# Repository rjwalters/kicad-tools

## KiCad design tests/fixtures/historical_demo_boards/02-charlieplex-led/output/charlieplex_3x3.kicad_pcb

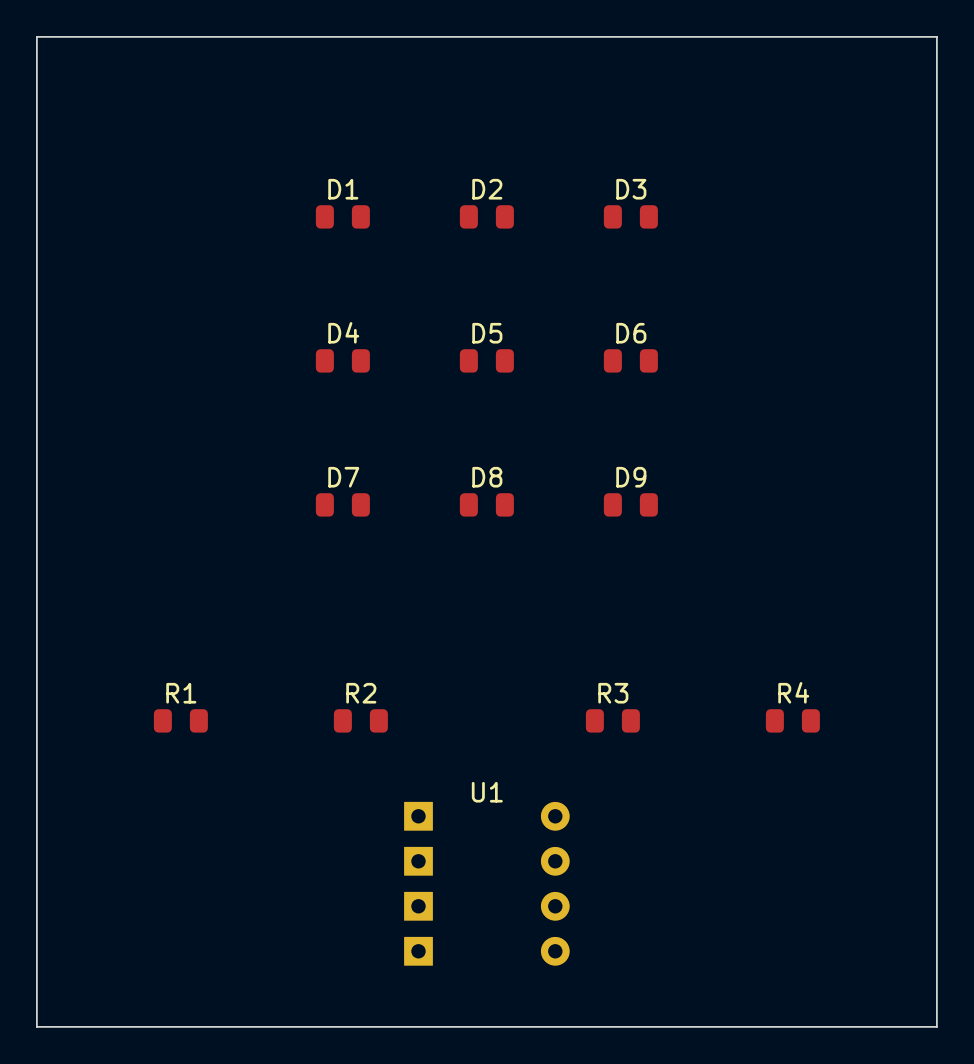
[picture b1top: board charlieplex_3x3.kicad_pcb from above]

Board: 2 copper layers, 50.0 x 55.0 mm, 14 parts (0 on the bottom side), 9 nets, no tracks yet.

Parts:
D1, D2, D3, D4, D5, D6, D7, D8, D9: LED; LED_0805_2012Metric
R1, R2, R3, R4: 330R; R_0805_2012Metric
U1: MCU; DIP-8_W7.62mm

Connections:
GND: U1.5, U1.6, U1.8
LINE_A: R1.1, U1.1
LINE_B: R2.1, U1.2
LINE_C: R3.1, U1.3
LINE_D: R4.1, U1.4
NODE_A: D1.2, D2.1, D3.2, D4.1, D5.2, D6.1, R1.2
NODE_B: D1.1, D2.2, D7.2, D8.1, D9.2, R2.2
NODE_C: D3.1, D4.2, D7.1, D8.2, R3.2
NODE_D: D5.1, D6.2, D9.1, R4.2

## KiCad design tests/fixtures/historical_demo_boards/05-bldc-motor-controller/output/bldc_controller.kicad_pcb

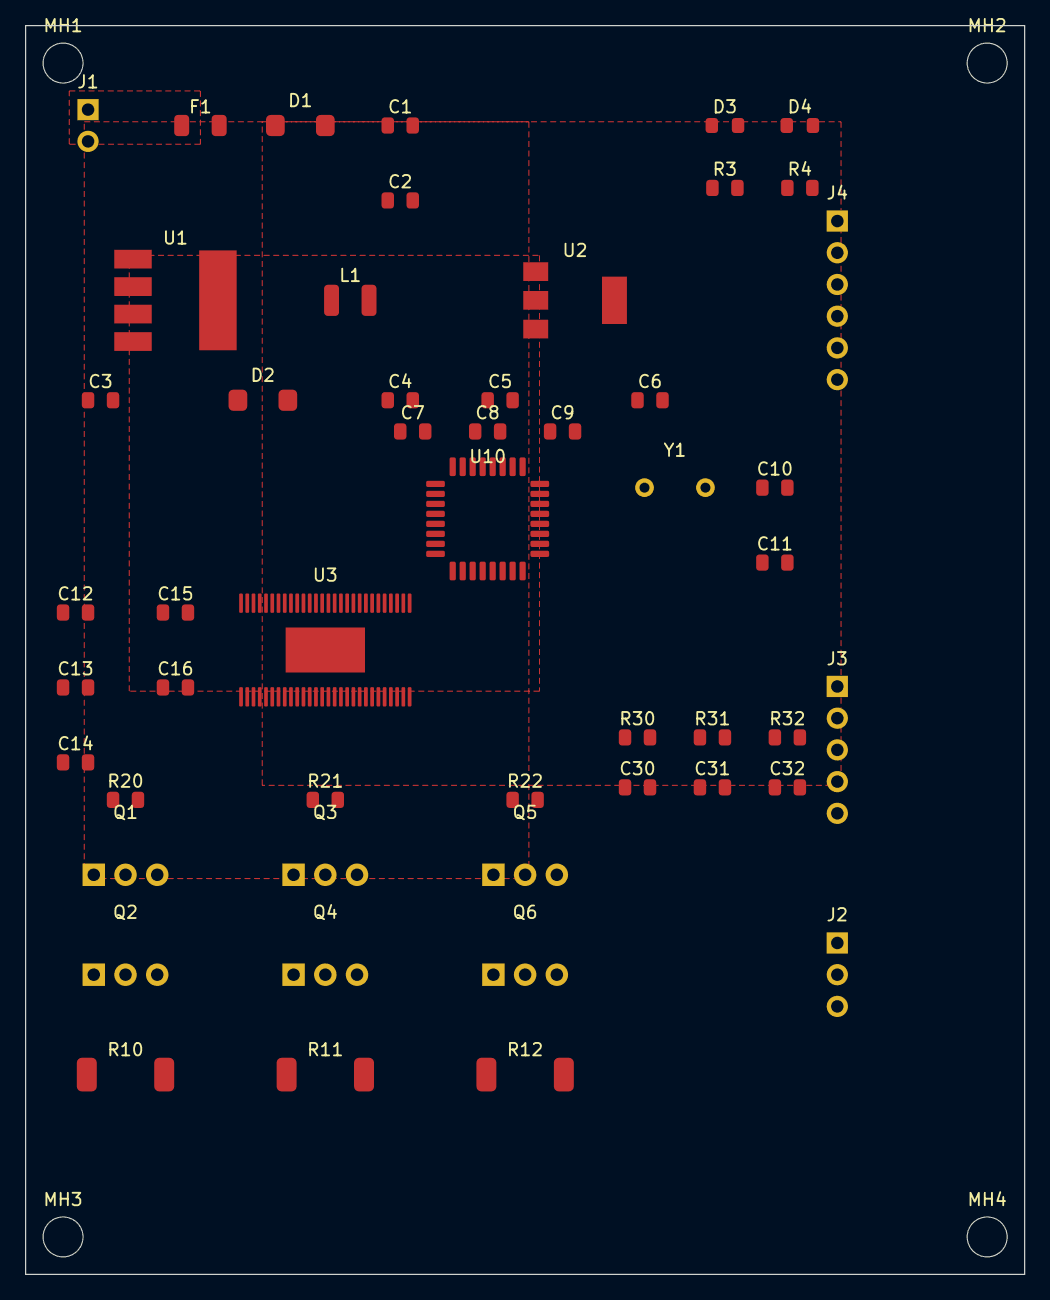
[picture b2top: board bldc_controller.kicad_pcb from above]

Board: 2 copper layers, 80.0 x 100.0 mm, 55 parts (0 on the bottom side), 44 nets, no tracks yet.

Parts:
C1: 470uF; C_0805_2012Metric
C2, C7, C8, C12, C13, C14, C15: 100nF; C_0805_2012Metric
C3, C4: 220uF; C_0805_2012Metric
C5, C6, C16: 10uF; C_0805_2012Metric
C9: 4.7uF; C_0805_2012Metric
C10, C11: 20pF; C_0805_2012Metric
C30, C31, C32: 10nF; C_0805_2012Metric
D1: SMBJ24A; D_SMA
D2: SS34; D_SMA
D3: PWR; LED_0805_2012Metric
D4: STATUS; LED_0805_2012Metric
F1: 15A; Fuse_1206_3216Metric
J1: Power Input; PinHeader_1x02_P2.54mm_Vertical
J2: Motor Output; PinHeader_1x03_P2.54mm_Vertical
J3: Hall Sensors; PinHeader_1x05_P2.54mm_Vertical
J4: SWD-6; PinHeader_1x06_P2.54mm_Vertical
L1: 33uH; L_1210_3225Metric
MH1, MH2, MH3, MH4: MountingHole; MountingHole_3.2mm_M3
Q1, Q2, Q3, Q4, Q5, Q6: IRLZ44N; TO-220-3_Vertical
R3, R4: 1k; R_0805_2012Metric
R10, R11, R12: 5mR; R_2512_6332Metric
R20, R21, R22: 22; R_0805_2012Metric
R30, R31, R32: 10k; R_0805_2012Metric
U1: LM2596-5.0; TO-263-5_TabPin3
U2: AMS1117-3.3; SOT-223-3_TabPin2
U3: DRV8301; HTSSOP-56-1EP_6.1x14mm_P0.5mm_EP3.61x6.35mm
U10: STM32G431K8Tx; LQFP-32_7x7mm_P0.8mm
Y1: 8MHz; Crystal_HC49-4H_Vertical

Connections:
+3V3: C6.1, C7.1, C8.1, C9.1, D3.2, D4.2, J3.4, J4.1, R30.1, R31.1, R32.1, U2.2, U3.4, U3.5, U3.6, U3.8, U3.9, U3.10, U3.11, U3.16, U3.23, U3.24, U3.49, U3.55, U10.1, U10.15, U10.17
+5V: C4.1, C5.1, C15.1, C16.1, L1.2, U1.4, U2.3, U3.3, U3.13, U3.14, U3.15, U3.27
+24V: C1.1, C2.1, C3.1, D1.1, F1.2, Q1.2, Q3.2, Q5.2, U1.1, U3.29, U3.52, U3.53, U3.54
BST_A: C14.1, U3.48
BST_B: C13.1, U3.43
BST_C: C12.1, U3.38
GATE_AH: Q5.1, R22.2
GATE_AL: Q6.1, U3.45
GATE_BH: Q3.1, R21.2
GATE_BL: Q4.1, U3.40
GATE_CH: Q1.1, R20.2
GATE_CL: Q2.1, U3.35
GATE_DRV_AH: R22.1, U3.47
GATE_DRV_BH: R21.1, U3.42
GATE_DRV_CH: R20.1, U3.37
GND: C1.2, C2.2, C3.2, C4.2, C5.2, C6.2, C7.2, C8.2, C9.2, C10.2, C11.2, C15.2, C16.2, C30.2, C31.2, C32.2, D1.2, D2.2, J1.2, J3.5, J4.6, R3.2, R4.2, U1.3, U1.5, U2.1, U3.1, U3.2, U3.7, U3.12, U3.28, U3.56, U3.57, U10.14, U10.16, U10.32
HALL_A: C30.1, J3.1, R30.2, U10.11
HALL_B: C31.1, J3.2, R31.2, U10.12
HALL_C: C32.1, J3.3, R32.2, U10.13
ISENSE_A+: Q6.3, R12.1, U3.25, U3.32
ISENSE_A-: R12.2, U3.33, U3.44, U10.5
ISENSE_B+: Q4.3, R11.1, U3.26, U3.30
ISENSE_B-: R11.2, U3.31, U3.39, U10.6
ISENSE_C+: Q2.3, R10.1
ISENSE_C-: R10.2, U3.34, U10.7
NRST: J4.5, U10.4
OSC_IN: C10.1, U10.2, Y1.1
OSC_OUT: C11.1, U10.3, Y1.2
PHASE_A: C14.2, J2.3, Q5.3, Q6.2, U3.46
PHASE_B: C13.2, J2.2, Q3.3, Q4.2, U3.41
PHASE_C: C12.2, J2.1, Q1.3, Q2.2, U3.36
PWM_AH: U3.17, U10.18
PWM_AL: U3.18, U10.29
PWM_BH: U3.19, U10.19
PWM_BL: U3.20, U10.30
PWM_CH: U3.21, U10.20
PWM_CL: U3.22, U10.31
PWR_LED: D3.1, R3.1
STATUS_LED: D4.1, R4.1
SWCLK: J4.3, U10.24
SWDIO: J4.2, U10.23
SWO: J4.4, U10.26
SW_OUT: D2.1, L1.1, U1.2, U3.50, U3.51
VIN: F1.1, J1.1
